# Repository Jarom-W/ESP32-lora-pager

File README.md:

# ESP32-lora-pager
Source code and supporting files for the ESP32 LoRa powered paging device. Uses standard LoRa frequency of 915MHz to send short range text messages.

LoRa_Enclosure_Design_Pack_Prototype -> The 3D printed prototype case and all related files.

firmware.ino -> Source code firmware written in the Arduino IDE

pager.kicad_pcb -> KiCad PCB file

pager.kicad_pro -> KiCad Project file

pager.kicad_sch -> KiCad PCB schematic

gerbers.zip -> Gerbers for ordering PCB from a fab

print.pdf -> Printed render of the final PCB.

Pager_Enclosure_Final.3mf -> Final design of the device enclosure

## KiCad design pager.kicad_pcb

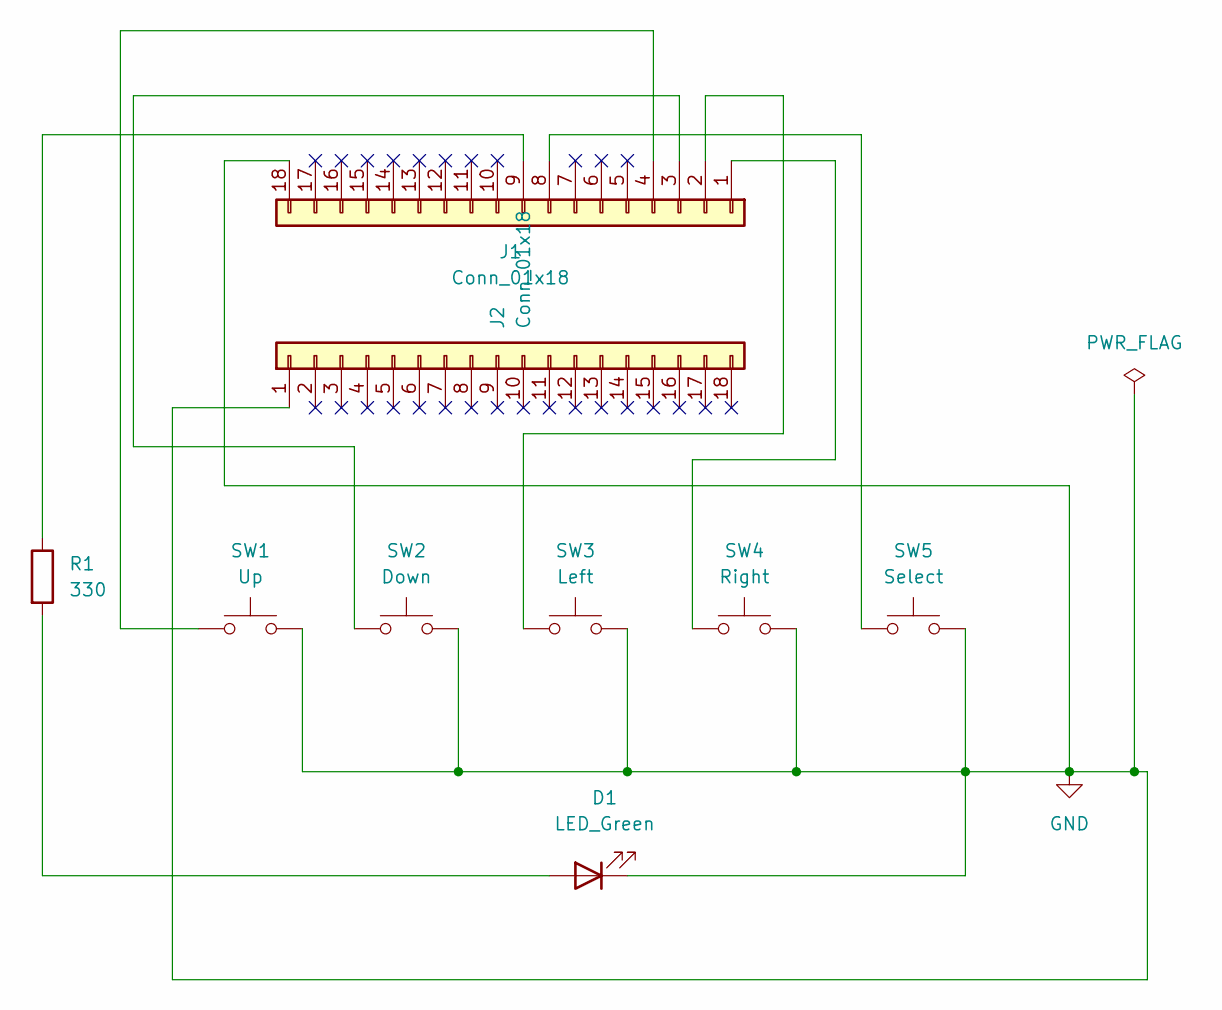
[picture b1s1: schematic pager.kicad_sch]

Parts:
D1: LED_Green; LED_D5.0mm
J1, J2: Conn_01x18; PinSocket_1x18_P2.54mm_Vertical
R1: 330; R_Axial_DIN0207_L6.3mm_D2.5mm_P7.62mm_Horizontal
SW1: Up; SW_PUSH_6mm
SW2: Down; SW_PUSH_6mm
SW3: Left; SW_PUSH_6mm
SW4: Right; SW_PUSH_6mm
SW5: Select; SW_PUSH_6mm

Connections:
GND: D1.1 (K), J1.18, J2.1, SW1.2, SW2.2, SW3.2, SW4.2, SW5.2
unnamed: D1.2 (A), R1.2
unnamed: J1.1, SW4.1
unnamed: J1.2, SW3.1
unnamed: J1.3, SW2.1
unnamed: J1.4, SW1.1
unnamed: J1.8, SW5.1
unnamed: J1.9, R1.1

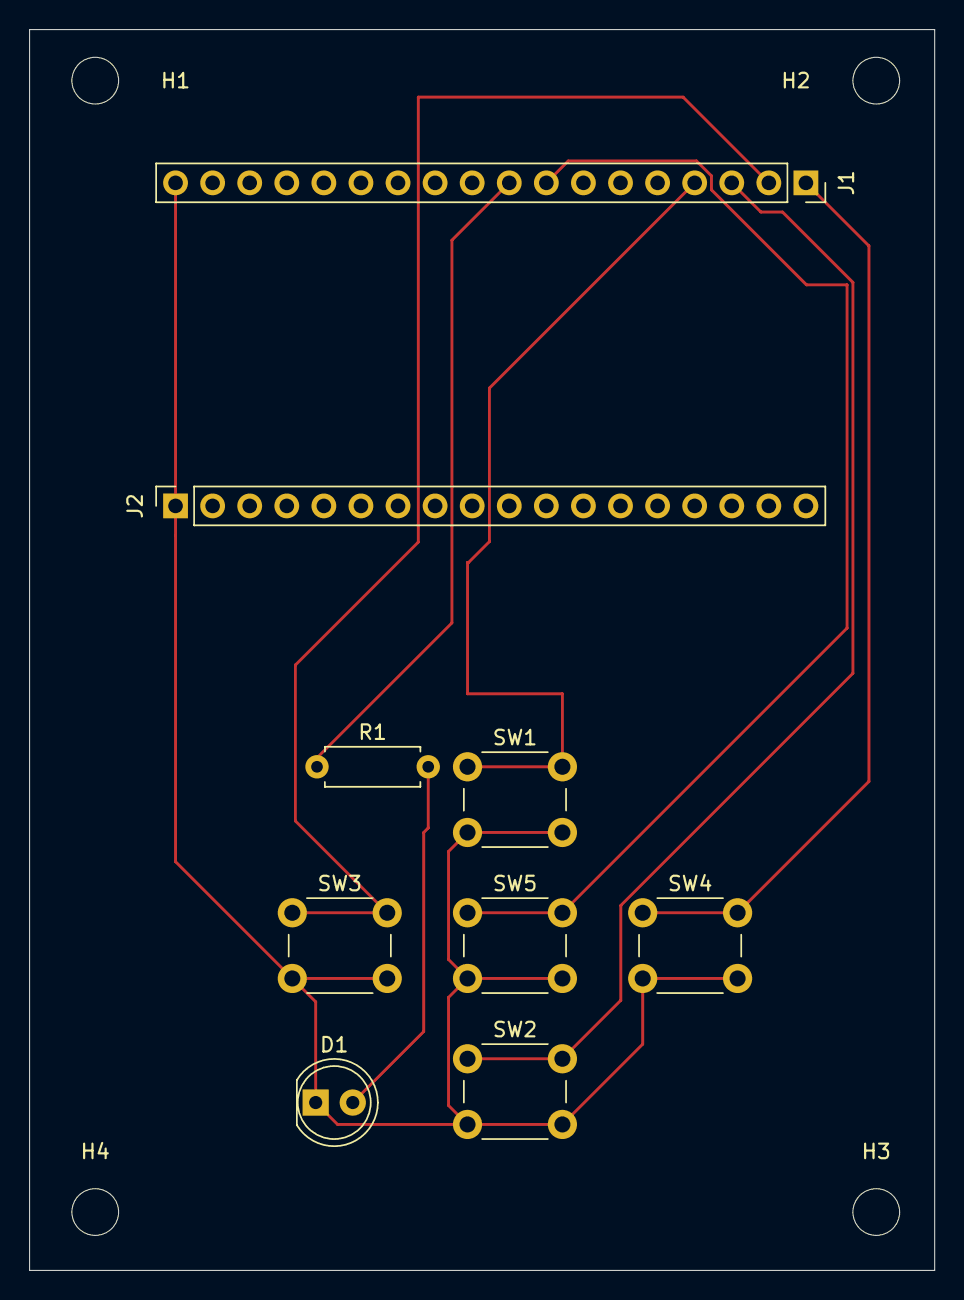
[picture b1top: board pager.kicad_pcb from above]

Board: 2 copper layers, 62.0 x 85.0 mm, 13 parts (0 on the bottom side), 8 nets.

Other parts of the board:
H1, H2, H3, H4: MountingHole_3.2mm_M3
